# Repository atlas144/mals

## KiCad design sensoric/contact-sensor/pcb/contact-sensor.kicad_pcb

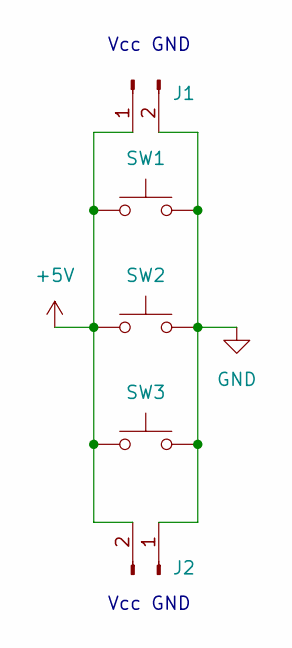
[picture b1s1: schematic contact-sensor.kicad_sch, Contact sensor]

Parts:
J1, J2: Conn_01x02_Male; PinHeader_1x02_P2.54mm_Horizontal
SW1, SW2, SW3: SW_Push; SW_PUSH_6mm_H7.3mm

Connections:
+5V: J1.1, J2.2, SW1.1, SW2.1, SW3.1
GND: J1.2, J2.1, SW1.2, SW2.2, SW3.2

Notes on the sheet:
Vcc GND

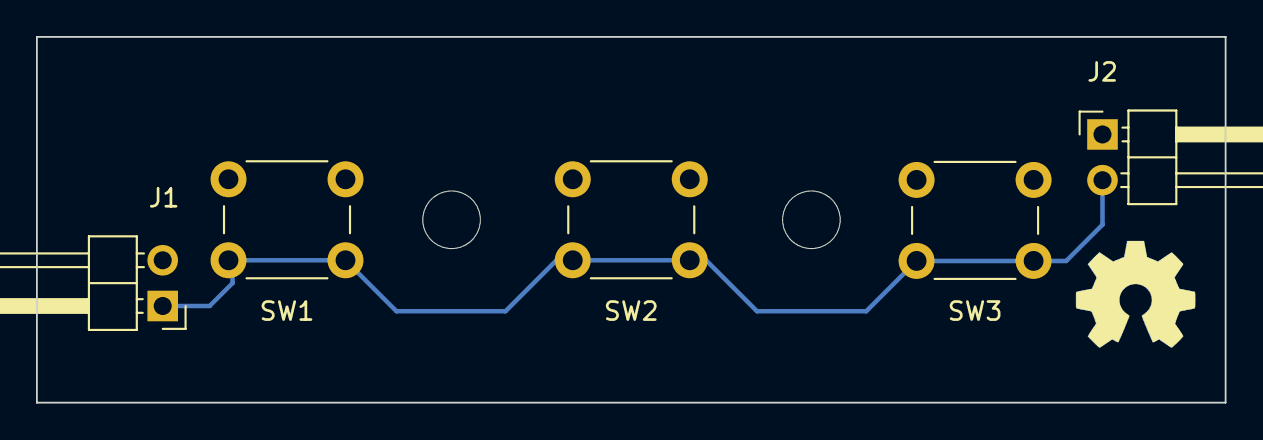
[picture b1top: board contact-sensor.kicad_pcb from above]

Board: 2 copper layers, 66.0 x 20.3 mm, 8 parts (1 on the bottom side), 2 nets.

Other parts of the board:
REF1, REF2: MountingHole_3.2mm_M3
REF3: OSHW-Symbol_6.7x6mm_Copper

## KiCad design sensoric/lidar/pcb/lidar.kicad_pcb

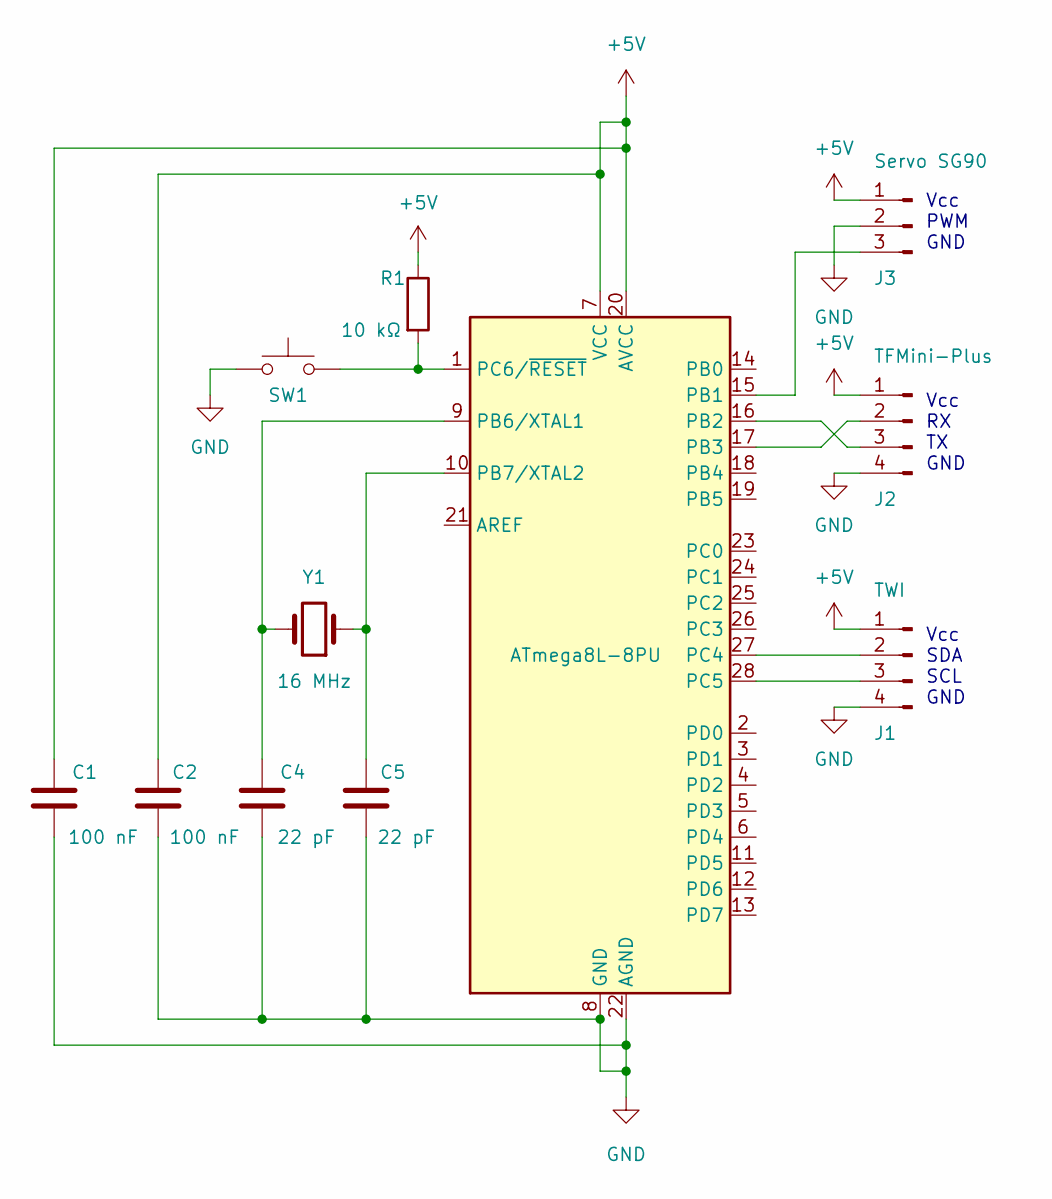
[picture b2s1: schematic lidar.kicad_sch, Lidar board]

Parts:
C1, C2: 100 nF; C_Disc_D4.3mm_W1.9mm_P5.00mm
C4, C5: 22 pF; C_Disc_D4.3mm_W1.9mm_P5.00mm
J1: TWI; Molex_KK-254_AE-6410-04A_1x04_P2.54mm_Vertical
J2: TFMini-Plus; PinHeader_1x04_P2.54mm_Vertical
J3: Servo SG90; PinHeader_1x03_P2.54mm_Vertical
R1: 10 kΩ; R_Axial_DIN0207_L6.3mm_D2.5mm_P10.16mm_Horizontal
SW1: SW_Push; SW_PUSH_6mm_H5mm
U1: ATmega8L-8PU; DIP-28_W7.62mm_Socket
Y1: 16 MHz; Crystal_HC49-4H_Vertical

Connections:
+5V: C1.1, C2.1, J1.1, J2.1, J3.1, R1.1, U1.7 (VCC), U1.20 (AVCC)
GND: C1.2, C2.2, C4.2, C5.2, J1.4, J2.4, J3.2, SW1.1, U1.8 (GND), U1.22 (AGND)
unnamed: C4.1, U1.9 (PB6/XTAL1), Y1.2
unnamed: C5.1, U1.10 (PB7/XTAL2), Y1.1
unnamed: J1.2, U1.27 (PC4)
unnamed: J1.3, U1.28 (PC5)
unnamed: J2.2, U1.17 (PB3)
unnamed: J2.3, U1.16 (PB2)
unnamed: R1.2, SW1.2, U1.1 (PC6/~RESET)
unnamed: J3.3, U1.15 (PB1)

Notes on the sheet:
Vcc SDA SCL GND
Vcc RX TX GND
Vcc PWM GND

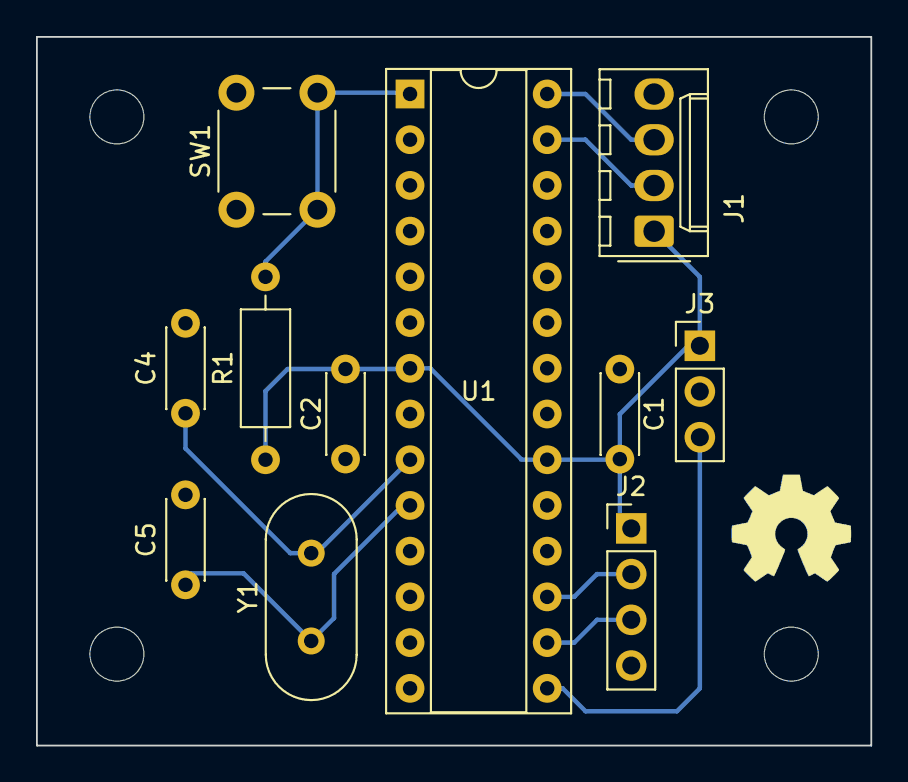
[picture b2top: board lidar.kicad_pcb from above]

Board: 2 copper layers, 46.4 x 39.4 mm, 17 parts (1 on the bottom side), 10 nets.

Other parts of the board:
OSHW - copper: OSHW-Symbol_6.7x6mm_Copper
OSHW - silk: OSHW-Symbol_6.7x6mm_SilkScreen
REF1, REF2, REF3, REF4: MountingHole_3mm

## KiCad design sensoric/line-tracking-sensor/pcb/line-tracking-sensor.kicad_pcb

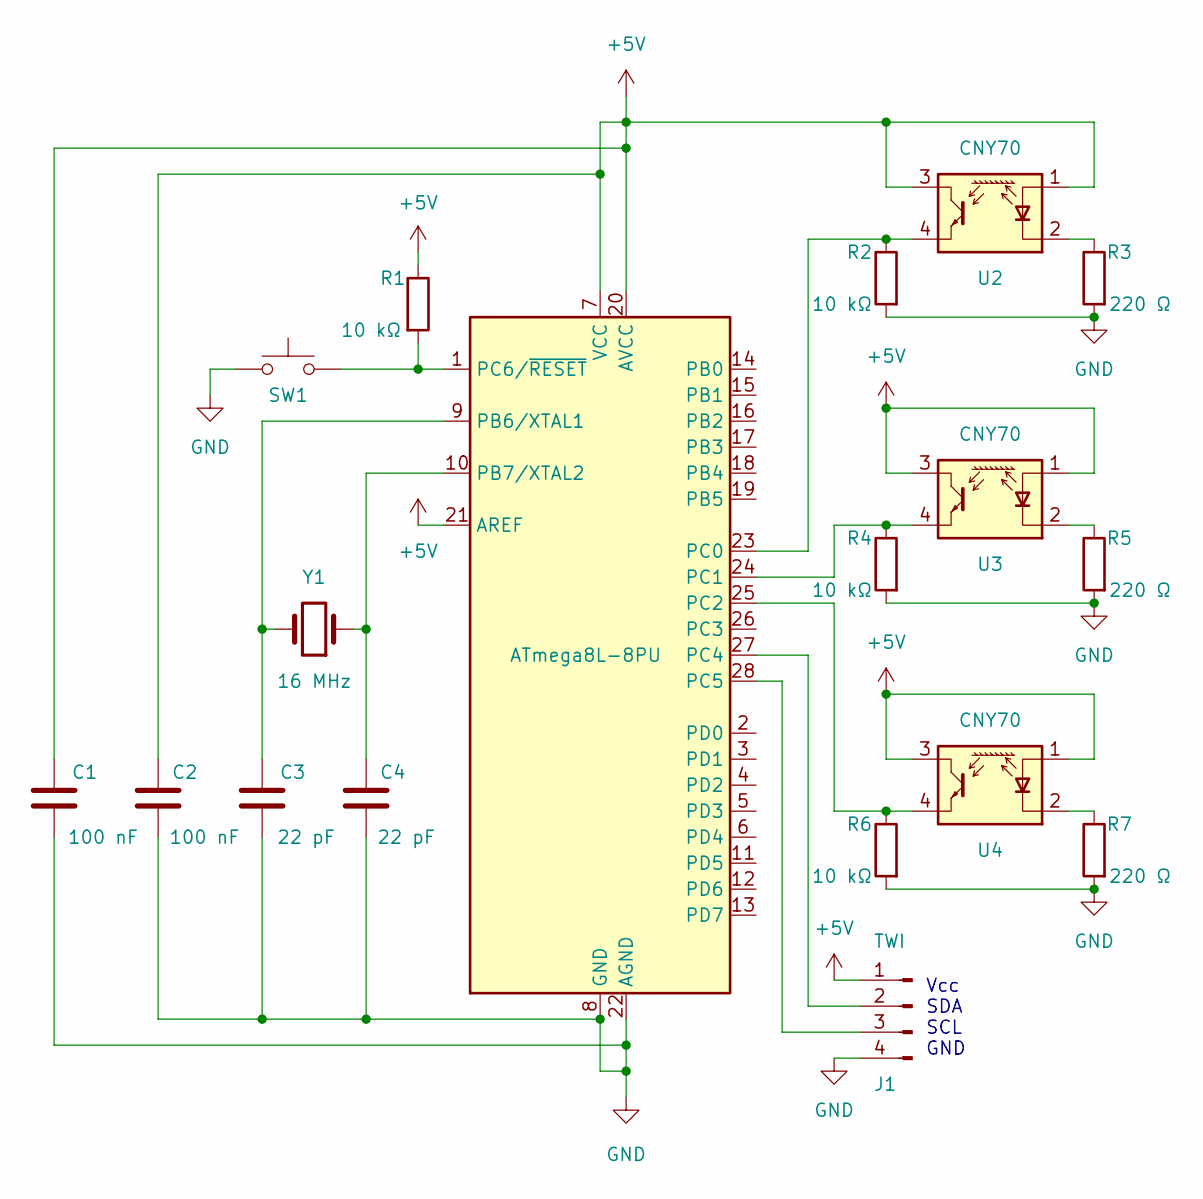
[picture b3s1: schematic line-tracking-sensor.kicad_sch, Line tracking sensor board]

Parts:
C1, C2: 100 nF; C_Disc_D4.3mm_W1.9mm_P5.00mm
C3, C4: 22 pF; C_Disc_D4.3mm_W1.9mm_P5.00mm
J1: TWI; Molex_KK-254_AE-6410-04A_1x04_P2.54mm_Vertical
R1, R2, R4, R6: 10 kΩ; R_Axial_DIN0207_L6.3mm_D2.5mm_P10.16mm_Horizontal
R3, R5, R7: 220 Ω; R_Axial_DIN0207_L6.3mm_D2.5mm_P10.16mm_Horizontal
SW1: SW_Push; SW_PUSH_6mm_H5mm
U1: ATmega8L-8PU; DIP-28_W7.62mm_Socket
U2, U3, U4: CNY70; Vishay_CNY70
Y1: 16 MHz; Crystal_HC49-4H_Vertical

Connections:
+5V: C1.1, C2.1, J1.1, R1.1, U1.7 (VCC), U1.20 (AVCC), U1.21 (AREF), U2.1 (A), U2.3 (C), U3.1 (A), U3.3 (C), U4.1 (A), U4.3 (C)
GND: C1.2, C2.2, C3.2, C4.2, J1.4, R2.2, R3.2, R4.2, R5.2, R6.2, R7.2, SW1.1, U1.8 (GND), U1.22 (AGND)
unnamed: C3.1, U1.9 (PB6/XTAL1), Y1.2
unnamed: C4.1, U1.10 (PB7/XTAL2), Y1.1
unnamed: R1.2, SW1.2, U1.1 (PC6/~RESET)
unnamed: R4.1, U1.24 (PC1), U3.4 (E)
unnamed: R6.1, U1.25 (PC2), U4.4 (E)
unnamed: J1.2, U1.27 (PC4)
unnamed: J1.3, U1.28 (PC5)
unnamed: R3.1, U2.2 (K)
unnamed: R2.1, U1.23 (PC0), U2.4 (E)
unnamed: R5.1, U3.2 (K)
unnamed: R7.1, U4.2 (K)

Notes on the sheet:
Vcc SDA SCL GND

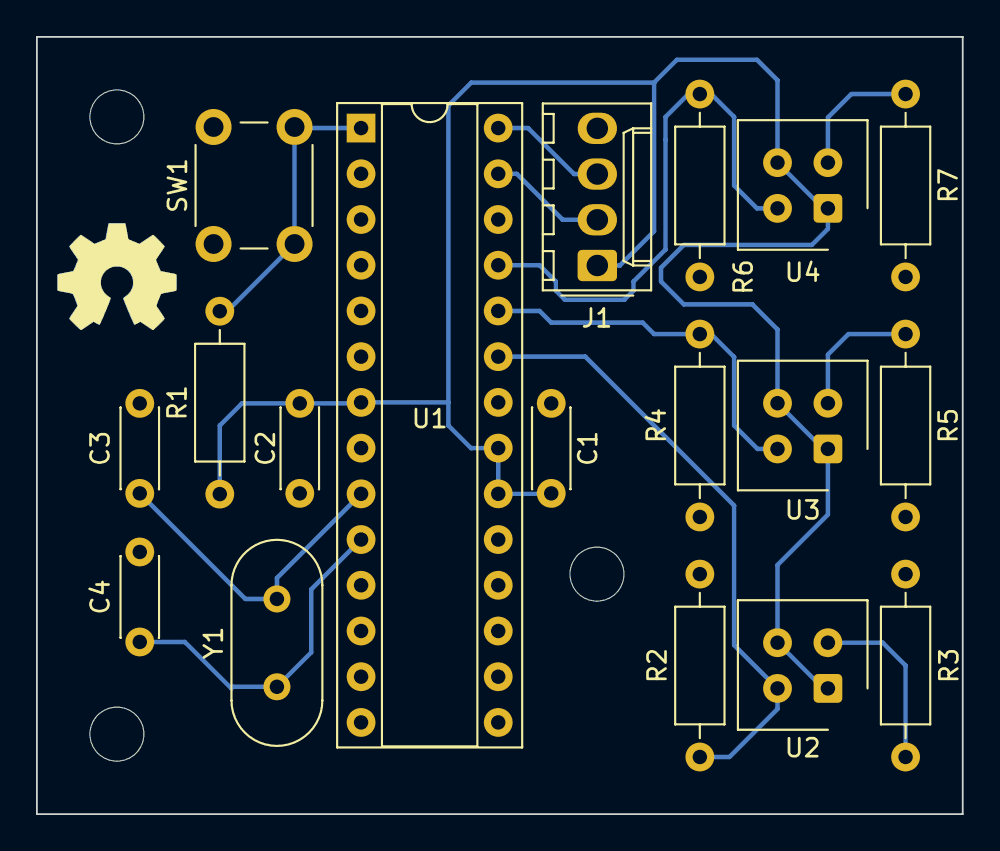
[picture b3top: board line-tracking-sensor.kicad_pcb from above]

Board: 2 copper layers, 51.4 x 43.2 mm, 23 parts (1 on the bottom side), 13 nets.

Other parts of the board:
REF1: OSHW-Symbol_6.7x6mm_Copper
REF2: OSHW-Symbol_6.7x6mm_SilkScreen
REF3, REF4, REF5: MountingHole_3mm

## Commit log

2021-09-12 added READMEs for submodules
2021-12-22 feature: component structure initialized
2021-12-29 refactor: main control program structure reinitialized
2022-01-03 feat: added MalsControlLibrary
2022-01-03 feat: sensor program initialized
2022-01-04 feat: lidar program initialized
2022-01-04 refactor: number of motor steps between measurements changed from hardcoded to dynamic value
2022-01-04 feature: sending motorSteps + distance (divided to 2 bytes)
2022-01-04 refactor: removed unnecessary statement
2022-01-04 refactor: removed unnecessary measurement cycle period bottleneck (changed from 20 to 100 Hz)
2022-01-05 refactor: changed structure to protothreading with Protorduino
2022-01-05 feat: added logging
2022-01-05 feat: sonars program initialized
2022-01-05 refactor: lidar - changed define to const
2022-01-05 refactor: added SW serial for lidar communication
2022-01-05 fix: fixed pin number collision and unrealistic time values
2022-01-05 docs: improved stepper logging
2022-01-08 refactor: renamed follow-line-sensor to line-tracking-sensor
2022-01-08 feat: added .gitignore for sensoric module
2022-01-08 feat: added "license" and "license user guide" for "lidar" sensor
2022-01-08 feat: added KiCad project files
2022-01-08 feat: added gerber and drill exports for "lidar" sensor
2022-01-08 feat: added visual exports for "lidar" sensor
2022-01-08 feat: added "license" and "license user guide" for "sonars" sensor
2022-01-08 feat: added KiCad project files for "sonars" sensor
2022-01-08 feat: added gerber and drill exports for "sonars" sensor
2022-01-08 feat: added visual exports for "sonars" sensor
2022-01-08 feat: added "license" and "license user guide" for "line-tracking-sensor"
2022-01-08 feat: added KiCad project files for "line-tracking-sensor"
2022-01-08 feat: added gerber and drill exports for "line-tracking-sensor"
2022-01-08 feat: added visual exports for "line-tracking-sensor"
2022-01-10 refactor: renamed Subsystems to Subsystems control unit
2022-01-13 feat: subsystems control unit initialized
2022-01-13 feat: added "subsystems control unit" bumpers activation response
2022-01-13 feat: added GPS sensor to "subsystems control unit"
2022-01-31 feat: project initialized
2022-02-01 feat: added Modules board
2022-02-01 fix: added project files to .gitignore
2022-02-01 feat: added board Header
2022-02-01 style: removed prettier warnings
2022-02-03 refactor: migrated from TS to JS
2022-02-03 docs: added comments
2022-02-03 style: changed application title
2022-02-11 refactor: project properties updated
2022-02-11 feat: added SubsystemsControlUnitModule
2022-02-24 refactor: updated project dependencies
2022-02-27 feat: added SRSC communication support
2022-02-27 feat: updated .gitignore to cover Sensoric and Client subsystems
2022-03-01 fix: TWI addresses changed
2022-03-01 refactor: moved from stepper motor to servo
2022-03-07 feat: added visual exports
2022-03-07 feat: added production exports
2022-03-07 docs: added license files
2022-03-07 feat: added gitignore entry
2022-03-08 refactor: changed connection pin position for better chaining

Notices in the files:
sensoric/contact-sensor/pcb/contact-sensor.kicad_pcb:
SPDX-License-Identifier: CERN-OHL-S-2.0
